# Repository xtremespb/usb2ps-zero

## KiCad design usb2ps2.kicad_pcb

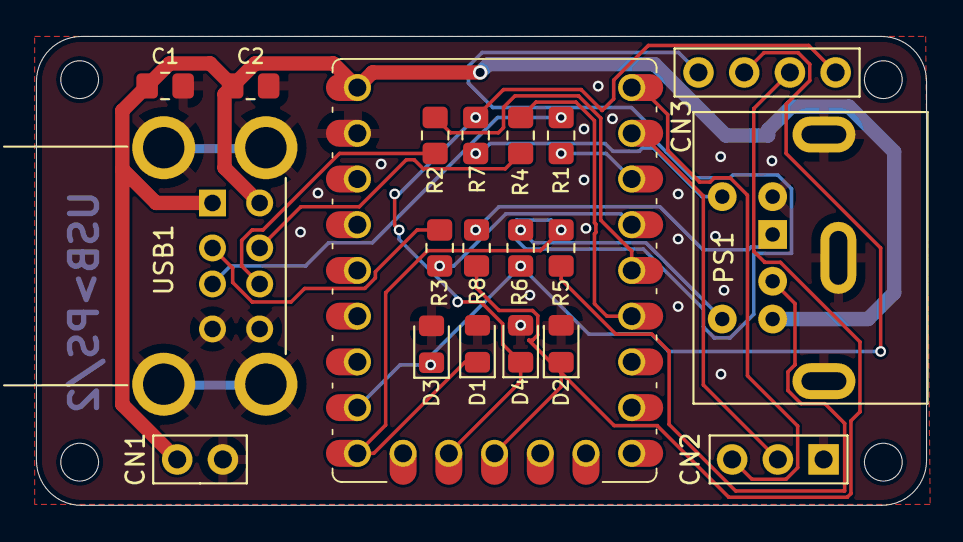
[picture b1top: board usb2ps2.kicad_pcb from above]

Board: 2 copper layers, 49.5 x 26.0 mm, 24 parts (0 on the bottom side), 20 nets.

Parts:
C1, C2: 10u; Medved_R_0805
CN1: Conn_01x02; Medved_PinHeader_1x02
CN2: UART; Medved_UART_Pin3
CN3: PS/2 Pins; Medved_PinHeader_1x04
D1, D2, D3, D4: 3V3; Medved_D_0805
H1, H2, H3, H4: MountingHole; MountingHole_2.1mm
PS1: PS/2; Connector_Mini-DIN_Female_6Pin_2rows
R1, R2, R3, R4: 22R; Medved_R_0805
R5, R6, R7, R8: 100R; Medved_R_0805
RP1: RP 2040 Zero; rp2040-zero-tht
USB1: USB_A_Stacked; Medved_USB_A_CUI_UJ2-ADH-TH_Horizontal_Stacked

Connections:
/GPIO0: CN2.1, RP1.1 (0)
/GPIO1: CN2.2, RP1.2 (1)
/GPIO2: R1.1, RP1.3 (2)
/GPIO3: R3.1, RP1.4 (3)
/GPIO4: R2.1, RP1.5 (4)
/GPIO5: R4.1, RP1.6 (5)
/GPIO11: CN3.2, D2.1 (K), R8.2, RP1.12 (11)
/GPIO12: CN3.1, D4.1 (K), R7.2, RP1.13 (12)
/GPIO14: CN3.4, D1.1 (K), R5.2, RP1.15 (14)
/GPIO15: CN3.3, D3.1 (K), R6.2, RP1.16 (15)
/PS2 with Diodes/KB_CLK: PS1.5, R7.1
/PS2 with Diodes/KB_DATA: PS1.1, R8.1
/PS2 with Diodes/MS_CLK: PS1.6, R6.1
/PS2 with Diodes/MS_DATA: PS1.2, R5.1
GND: C1.2, C2.2, CN1.2, CN2.3, D1.2 (A), D2.2 (A), D3.2 (A), D4.2 (A), PS1.3, RP1.22 (GND), USB1.4 (GND1), USB1.8 (GND2), USB1.9 (Shield)
unnamed: R1.2, USB1.3 (D1+)
unnamed: R3.2, USB1.2 (D1-)
unnamed: R2.2, USB1.7 (D2+)
unnamed: R4.2, USB1.6 (D2-)
VBUS: C1.1, C2.1, CN1.1, PS1.4, RP1.23 (5V), USB1.1 (VBUS1), USB1.5 (VBUS2)

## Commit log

2024-12-07 Initial commit (HW Rev 1.0)
2024-12-07 Added STEP file
2024-12-07 Added Gerber files
2024-12-08 HW Rev 1.0 minor updates
